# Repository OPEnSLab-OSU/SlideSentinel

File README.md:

# SlideSentinel

## How to Setup
Install the arduino IDE, follow the adafruit [guide](https://learn.adafruit.com/adafruit-feather-m0-basic-proto/overview), and install LOOM with it dependencies with its guide [here](https://github.com/OPEnSLab-OSU/InternetOfAg/tree/master/Arduino_and_Loom_Setup)

Building the rover and base:
Refer to the schematics in the documentation for building the rover and base. All pins are labeled in the schematic located in Documentation/ProjectSpecifications. Custom printed PCB schematics are located in Integration/Hardware/Base and /Rover. Building and creating of the hardware is managed by the OPEnS lab members. A full list of materials and parts used for all phases of the project is located in the supplemental documentation in the bill of materials (BOM). The software for the hub and nodes are located in "Integration/Base" and "Integration/Rover" respectivly. Load one of the directories into arduino IDE and attach whichever device you are building them compile and export to the arduino.

The spreadsheet visualizer and parser is located at "Integration/Spreadsheet". A setup guide is included within along with some sample data.

The node application which facilitates traffic from the Rock7 servers to google spreadsheets is located at "integration/POSTproxy". A setup guide is included within. The application is active at https://postproxy.azurewebsites.net/. 

The mapping application is located at "SlideSentinelWebClient/myapp". An installation guide is included. This application hooks into the spreadsheet and pulls data to display is on a map. An active version of the map is avaliable [here](http://home.stallkamp.us:8999)

## Directory Layout
- Devices contains development, testing, and drivers for specific devices in the system.
- Documentation contains an assortment of documentation including data sheets, blog posts, notes, and the capstone documentation.
- Integration contains mostly all the up to date and in use code for the project. Some directories within are backups of previous demonstrations of the system in different iterations.
- Phase 1 Legacy Code contains some old hub code when the project was just begining.
- SlideSentinelWebClient contains the node app for the mapping application.

# Slide Sentinel Project Specification Guide

## Base

Specification | Status 
--- | --- 
Power Budget | Draws 150-160mA 
Remote Configuration | Hub can recieve remote configuration data to control the satcom upload cycle time, set verbosity scale, and force a satcom uploads.
Deployment Duration | System must last for 1 month
Range | Base unit will be elevated with reference to the node, one mile distance apart, concrete base.

## Rover

Specification | Status
--- | --- 
Power Budget | Draws ~170 mA, 4.53 mA in low power mode 
Solar Power | Solar power charger supplies ~20mA in shaded enviroments and ~175 mA in direct sunlight
Positional Accuracy | Rover must generate sub-centimeter positional calculations at least once a day, with partial tree cover (RTK fix with RTK ratio of 10)
Deployment Duration | System must last 1 month at 15 minute wake cycles
Accelerometer | Sudden orientation shifts must wake Rover unit up from sleep and trigger positional calculations.

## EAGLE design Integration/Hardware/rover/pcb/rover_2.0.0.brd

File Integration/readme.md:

# Slide Sentinel Phase 1 Prototype

This folder contains all of the code for producing a new Rover and Base station pair. This device is intended for collecting data on landslide movement with sub-centimeter positional accuracy. The system logs rover position at set intervals, and uploads the highest quality positional fix via a satcom upload using the ROCKBLOCK+. 

## Getting Started

Inspect the Rover/Rover.png and Base/Base.png schemtic images for a detailed schematic of all components used in the system build. Using the Arduino IDE load the Base device with Base/Base.ino and the Rover device with Rover/Rover.ino. 

## Hardware

### Base
- ROCKBLOCK+ Iridium Satcom Module
- Freewave Z9-T radio
- RTK - GPS Base

### Rover
- MMA8451 accelerometer with interrups
- DS3231 real time clock with interrupts
- Datalogger
- Latching relay for power management
- Freewave Z9-T radio
- RTK - GPS Rover

## Files
1. **Base:** All files for the Base unit of the system
2. **Rover:** All files for the Rover unit for the system
3. **POSTproxy:** Source code for the post proxy web application. Required for successful Google Spreadsheets HTTP requests.
4. **Spreadsheet:** Google spreadsheet script for displaying recorded data.
5. **EditLib:** Rover unit contains direct library edits. This folder contains copies of editted library files, and original copies of library files for the Base unit.

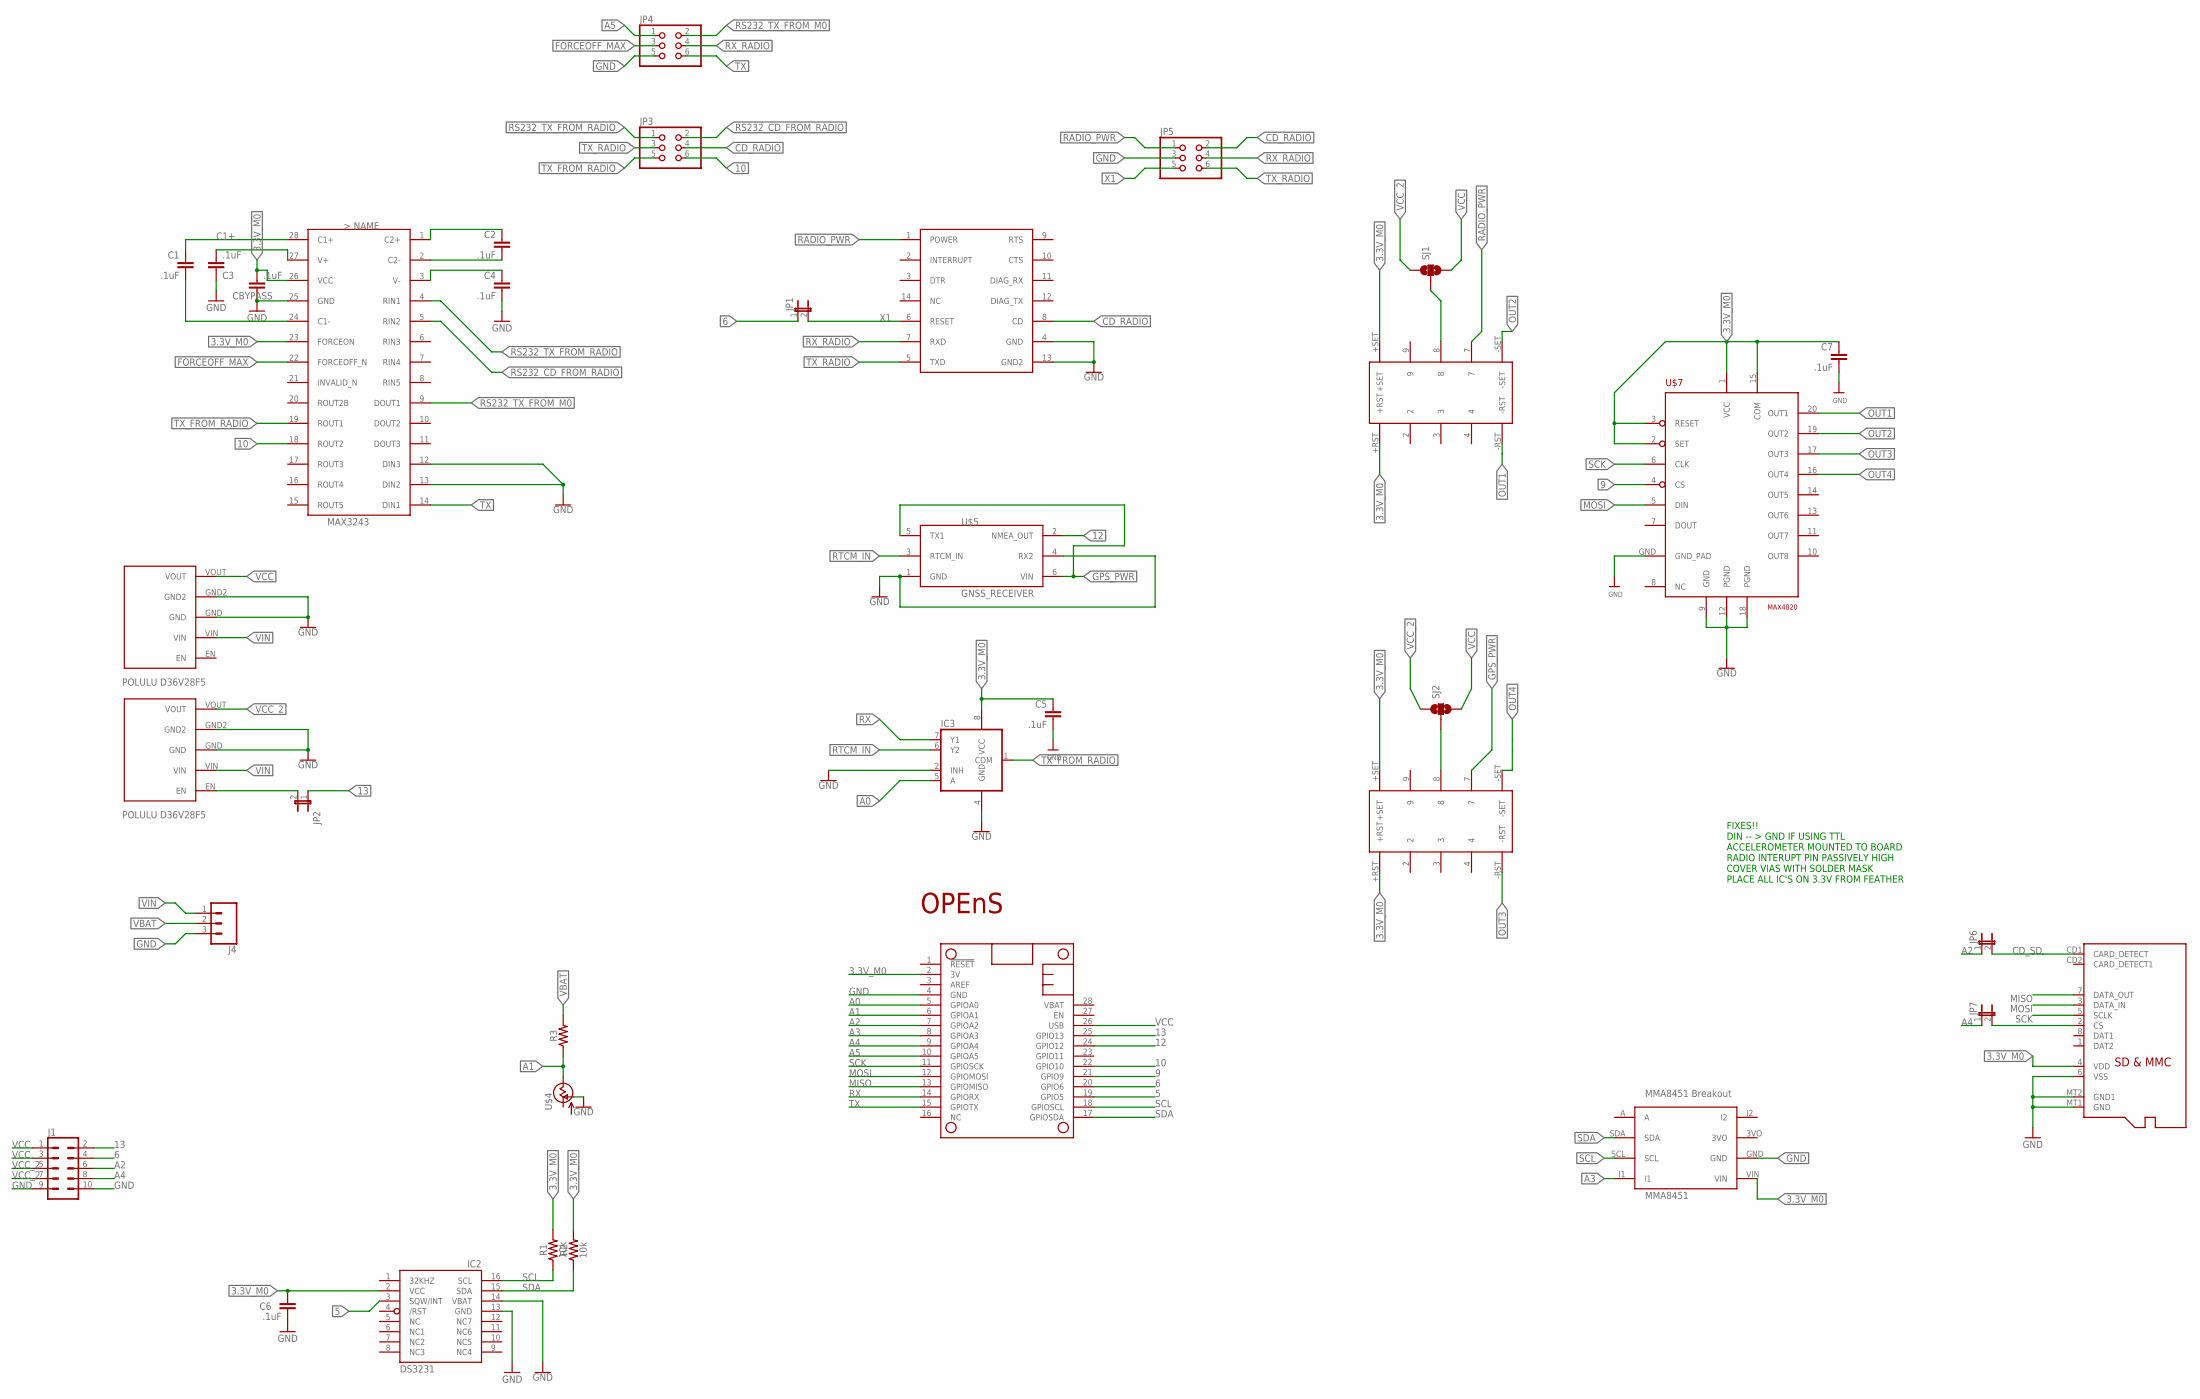
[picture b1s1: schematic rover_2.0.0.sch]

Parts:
C1, C2, C3, C4, C5, C6, C7: .1uF; C1206
CBYPASS: .1uF; C1206
IC2: DS3231/SO; SO16W
IC3: 741G53DCT; DCT_R-PDSO-G8
J1: CONN_05X2NO_SILK; 2X5_NOSILK
J4: CONN_03SCREW; SCREWTERMINAL-3.5MM-3
JP1, JP2, JP6, JP7: JP1E; JP1
JP3, JP4, JP5: PINHD-2X3; 2X03
MS1: FEATHERWING
R1, R2: 10k; 0603
R3: 1.6KOHM-0603-1/10W-1%; 0603
SJ1, SJ2: SOLDERJUMPER_2WAY-OLDT; SJ_2
U$1: MAX3243; SSOP-28
U$2: OPENS-LOGO
U$3, U$12: POLULU_D36V28FX
U$4: CT6EP205; CT6
U$5: GNSS_RECEIVER; HDRV6W64P254_2X3_1016X508X838B
U$7: MAX4820; TSSOP20
U$8, U$9: TQ2SS
U$11: Z9-T/Z9-C
U$13: MMA8451
U$16: MICROSD

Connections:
3.3V_M0: C5.1, C6.1, C7.1, CBYPASS.2, IC2.2 (VCC), IC3.8 (VCC), MS1.2 (3V), R1.2, R2.2, U$1.23 (FORCEON), U$1.26 (VCC), U$7.1 (VCC), U$7.2 (SET), U$7.3 (RESET), U$7.15 (COM), U$8.+RST, U$8.+SET, U$9.+RST, U$9.+SET, U$13.VIN, U$16.4 (VDD)
5: IC2.3 (SQW/INT), MS1.19 (GPIO5)
6: J1.4, JP1.1, MS1.20 (GPIO6)
9: MS1.21 (GPIO9), U$7.4 (CS)
10: JP3.6, MS1.22 (GPIO10), U$1.18 (ROUT2)
12: MS1.24 (GPIO12), U$5.2 (NMEA_OUT)
13: J1.2, JP2.1, MS1.25 (GPIO13)
A0: IC3.5 (A), MS1.5 (GPIOA0)
A1: MS1.6 (GPIOA1), R3.1, U$4.S (VSS)
A2: J1.6, JP6.1, MS1.7 (GPIOA2)
A3: MS1.8 (GPIOA3), U$13.I1
A4: J1.8, JP7.1, MS1.9 (GPIOA4)
A5: JP4.1, MS1.10 (GPIOA5)
C1+: C1.1, U$1.28 (C1+)
CD_RADIO: JP3.4, JP5.2, U$11.8 (CD)
CD_SD: JP6.2, U$16.CD1 (CARD_DETECT)
CS_SD: JP7.2, U$16.2 (CS)
FORCEOFF_MAX: JP4.3, U$1.22 (FORCEOFF_N)
GND: C3.1, C4.2, C5.2, C6.2, C7.2, CBYPASS.1, IC2.13 (GND), IC2.14 (VBAT), IC3.2 (INH), IC3.4 (GND), J1.9, J1.10, J4.3, JP4.5, JP5.3, MS1.4 (GND), U$1.12 (DIN3), U$1.13 (DIN2), U$1.25 (GND), U$3.GND, U$3.GND2, U$4.A (OUT), U$5.1 (GND), U$5.4 (RX2), U$7.9 (GND), U$7.12 (PGND), U$7.18 (PGND), U$7.GND (GND_PAD), U$11.4 (GND), U$11.13 (GND2), U$12.GND, U$12.GND2, U$13.GND, U$16.6 (VSS), U$16.MT1 (GND), U$16.MT2 (GND1)
GPS_PWR: U$5.5 (TX1), U$5.6 (VIN), U$9.7
MISO: MS1.13 (GPIOMISO), U$16.7 (DATA_OUT)
MOSI: MS1.12 (GPIOMOSI), U$7.5 (DIN), U$16.3 (DATA_IN)
unnamed: SJ2.2, U$9.8
unnamed: SJ1.2, U$8.8
unnamed: C2.1, U$1.1 (C2+)
unnamed: C2.2, U$1.2 (C2-)
unnamed: C4.1, U$1.3 (V-)
unnamed: C1.2, U$1.24 (C1-)
unnamed: C3.2, U$1.27 (V+)
OUT1: U$7.20 (OUT1), U$8.-RST
OUT2: U$7.19 (OUT2), U$8.-SET
OUT3: U$7.17 (OUT3), U$9.-RST
OUT4: U$7.16 (OUT4), U$9.-SET
RADIO_PWR: JP5.1, U$8.7, U$11.1 (POWER)
RS232_CD_FROM_RADIO: JP3.2, U$1.5 (RIN2)
RS232_TX_FROM_M0: JP4.2, U$1.9 (DOUT1)
RS232_TX_FROM_RADIO: JP3.1, U$1.4 (RIN1)
RTCM_IN: IC3.6 (Y2), U$5.3 (RTCM_IN)
RX: IC3.7 (Y1), MS1.14 (GPIORX)
RX_RADIO: JP4.4, JP5.4, U$11.7 (RXD)
SCK: MS1.11 (GPIOSCK), U$7.6 (CLK), U$16.5 (SCLK)
SCL: IC2.16 (SCL), MS1.18 (GPIOSCL), R1.1, U$13.SCL
SDA: IC2.15 (SDA), MS1.17 (GPIOSDA), R2.1, U$13.SDA
TX: JP4.6, MS1.15 (GPIOTX), U$1.14 (DIN1)
TX_FROM_RADIO: IC3.1 (COM), JP3.5, U$1.19 (ROUT1)
TX_RADIO: JP3.3, JP5.6, U$11.5 (TXD)
VBAT: J4.2, R3.2
VCC: J1.1, J1.3, MS1.26 (USB), SJ1.3, SJ2.3, U$3.VOUT
VCC_2: J1.5, J1.7, SJ1.1, SJ2.1, U$12.VOUT
VIN: J4.1, U$3.VIN, U$12.VIN
X1: JP1.2, JP5.5, U$11.6 (RESET)
X2: JP2.2, U$12.EN

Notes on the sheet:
FIXES!! DIN -- > GND IF USING TTL ACCELEROMETER MOUNTED TO BOARD RADIO INTERUPT PIN PASSIVELY HIGH COVER VIAS WITH SOLDER MASK PLACE ALL IC'S ON 3.3V FROM FEATHER

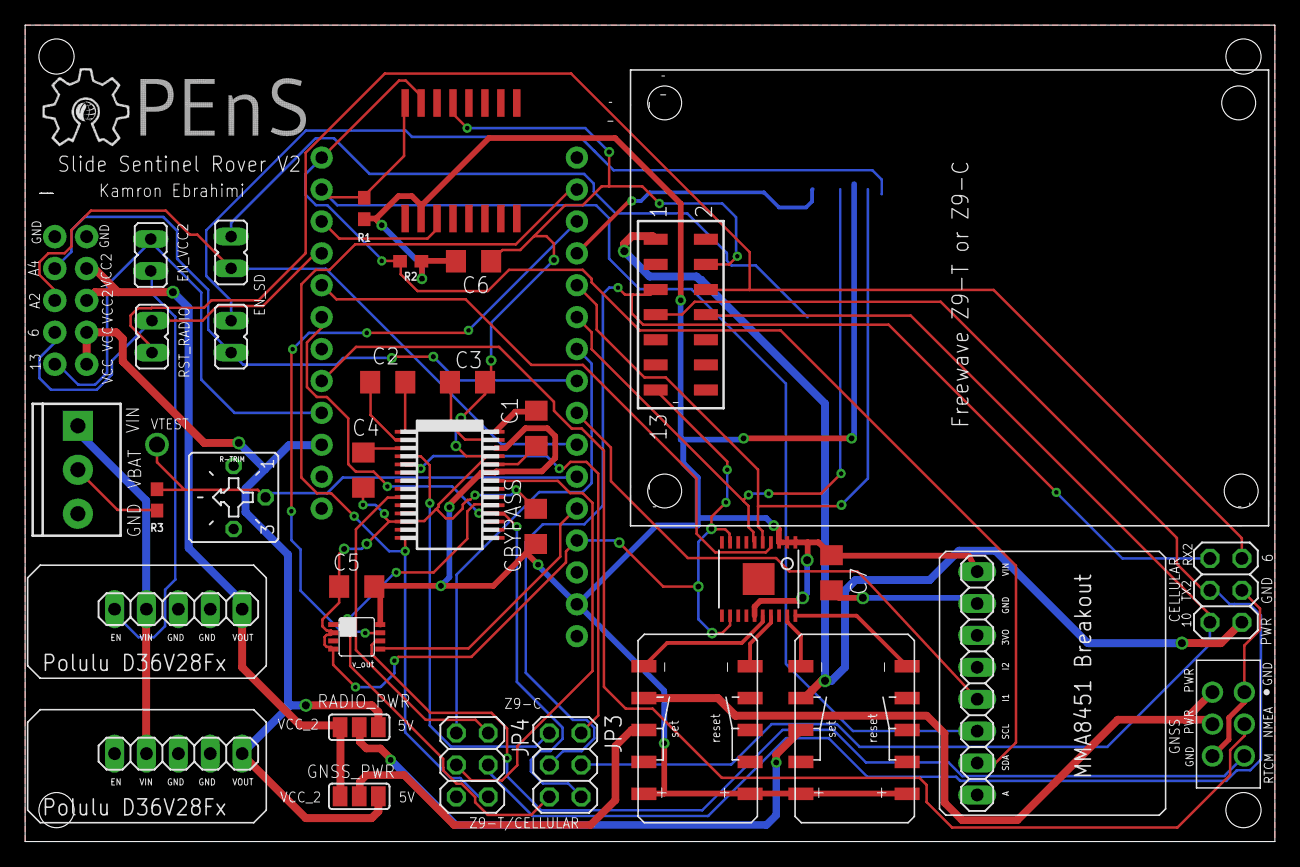
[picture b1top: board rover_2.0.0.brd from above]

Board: 2 copper layers, 99.5 x 65.0 mm, 37 parts (1 on the bottom side), 52 nets.

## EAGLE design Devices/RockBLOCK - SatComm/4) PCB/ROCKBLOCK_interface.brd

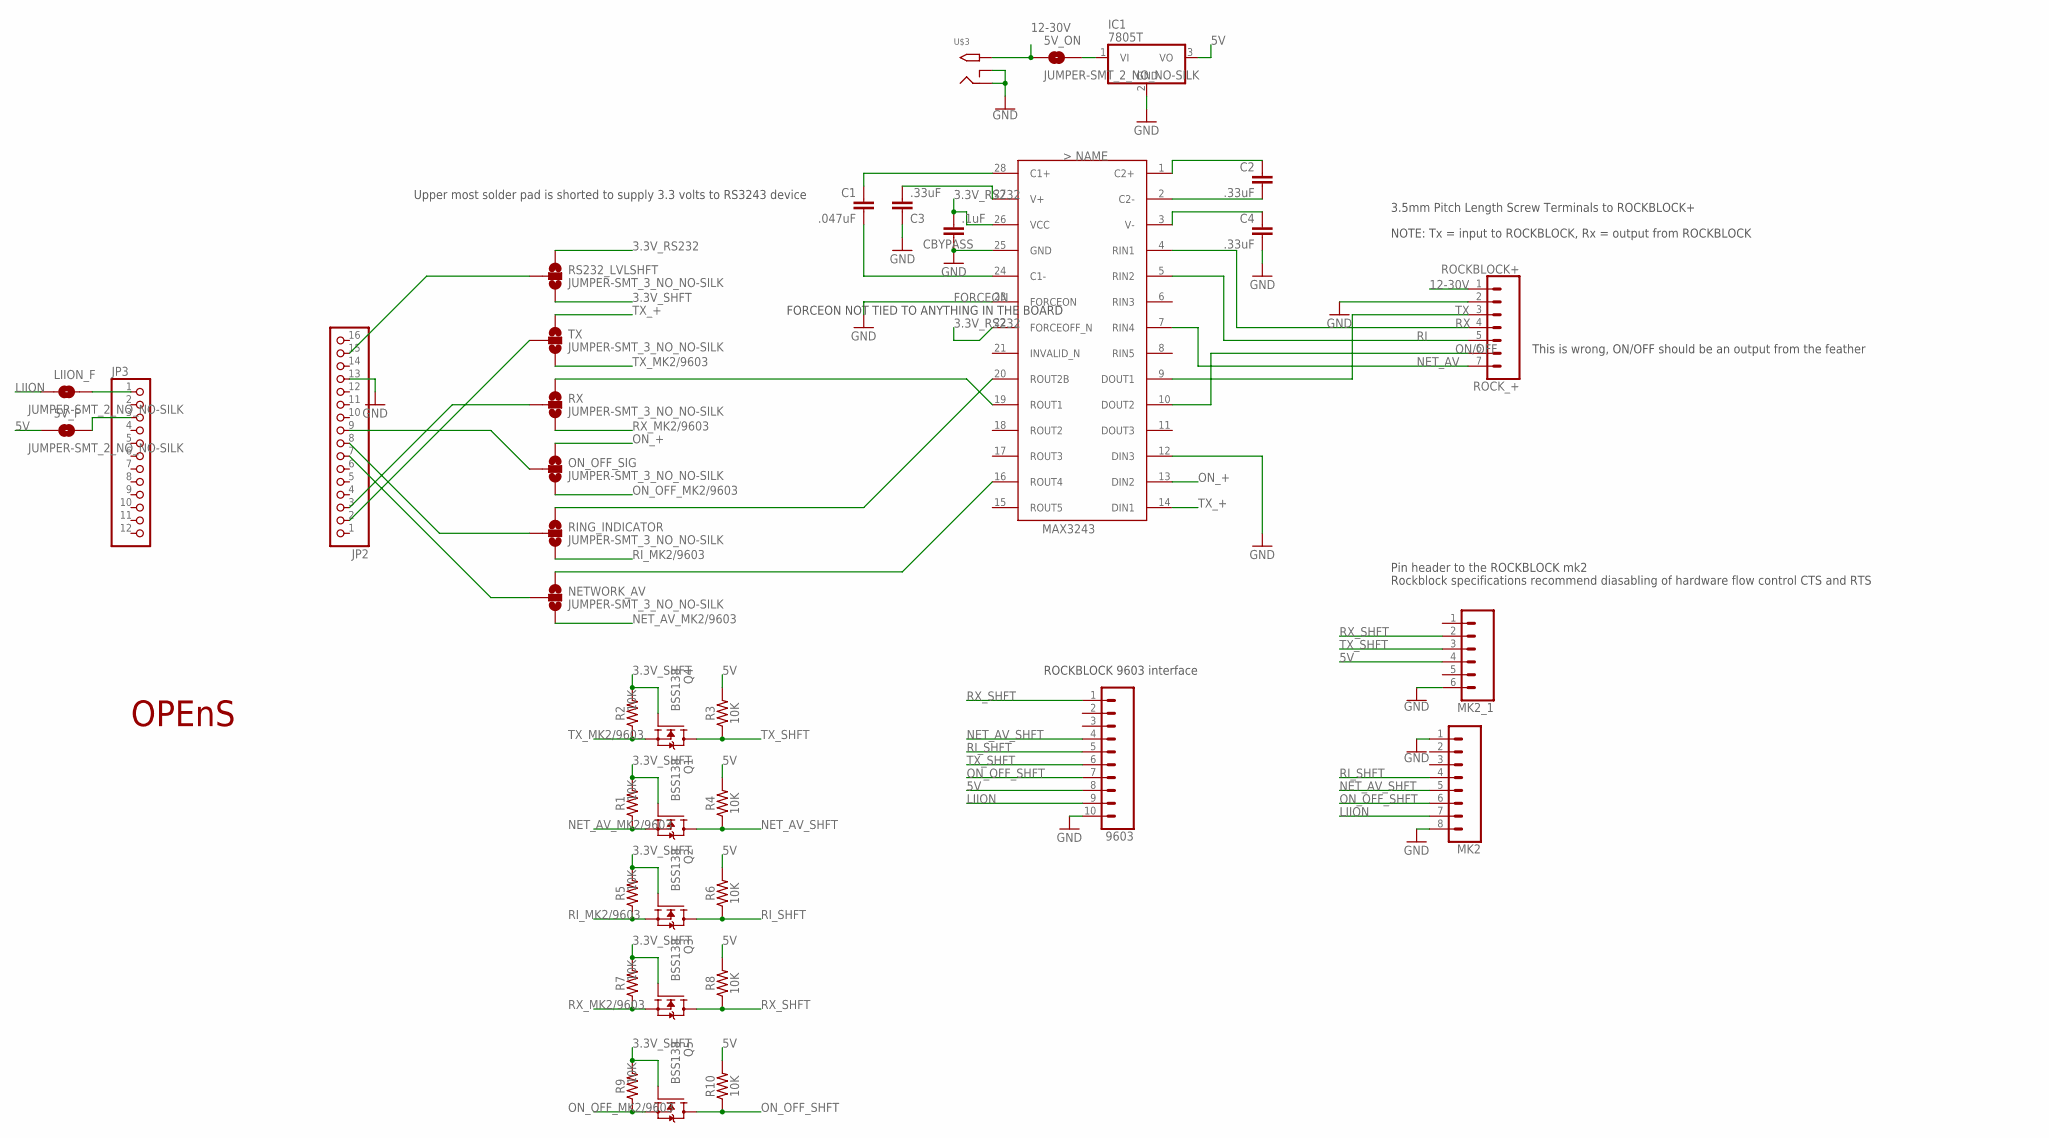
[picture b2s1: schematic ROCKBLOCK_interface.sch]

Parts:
5V_F, 5V_ON: JUMPER-SMT_2_NO_NO-SILK; SMT-JUMPER_2_NO_NO-SILK
9603: CONN_10"; 1X10
C1: .047uF; C1206
C2, C3, C4: .33uF; C1206
CBYPASS: .1uF; C1206
IC1: 7805T; TO220H
JP2: PINHD-1X16; 1X16
JP3: PINHD-1X12; 1X12
LIION_F: JUMPER-SMT_2_NO_NO-SILK; SMT-JUMPER_2_NO_NO-SILK
MK2: CONN_08NO_SILK_FEMALE_PTH; 1X08_NO_SILK
MK2_1: CONN_06NO_SILK_FEMALE_PTH; 1X06_NO_SILK
NETWORK_AV: JUMPER-SMT_3_NO_NO-SILK; SMT-JUMPER_3_NO_NO-SILK
ON_OFF_SIG: JUMPER-SMT_3_NO_NO-SILK; SMT-JUMPER_3_NO_NO-SILK
Q1, Q2, Q3, Q4, Q5: BSS138; SOT23
R1, R2, R3, R4, R5, R6, R7, R8, R9, R10: 10K; 0603
RING_INDICATOR: JUMPER-SMT_3_NO_NO-SILK; SMT-JUMPER_3_NO_NO-SILK
ROCK_+: ROCKBLOCK+; SCREWTERMINAL-3.5MM-7
RS232_LVLSHFT: JUMPER-SMT_3_NO_NO-SILK; SMT-JUMPER_3_NO_NO-SILK
RX: JUMPER-SMT_3_NO_NO-SILK; SMT-JUMPER_3_NO_NO-SILK
TX: JUMPER-SMT_3_NO_NO-SILK; SMT-JUMPER_3_NO_NO-SILK
U$1: MAX3243; SSOP-28
U$2: OPENS-LOGO
U$3: 2.1MMJACKTHM; PJ-102A

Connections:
3.3V_RS232: CBYPASS.2, RS232_LVLSHFT.1, U$1.22 (FORCEOFF_N), U$1.26 (VCC)
3.3V_SHFT: Q1.1 (G), Q2.1 (G), Q3.1 (G), Q4.1 (G), Q5.1 (G), R1.2, R2.2, R5.2, R7.2, R9.2, RS232_LVLSHFT.3
5V: 5V_F.1, 9603.8, IC1.3 (VO), MK2_1.4, R3.2, R4.2, R6.2, R8.2, R10.2
12-30V: 5V_ON.1, ROCK_+.1, U$3.TIP
C1+: C1.1, U$1.28 (C1+)
FORCEON: U$1.23 (FORCEON)
GND: 9603.10, C3.1, C4.2, CBYPASS.1, IC1.2 (GND), JP2.13, MK2.1, MK2.8, MK2_1.6, ROCK_+.2, U$1.12 (DIN3), U$1.25 (GND), U$3.RING, U$3.RING_SW
LIION: 9603.9, LIION_F.1, MK2.7
unnamed: C2.1, U$1.1 (C2+)
unnamed: C2.2, U$1.2 (C2-)
unnamed: C4.1, U$1.3 (V-)
unnamed: JP2.2, TX.2
unnamed: 5V_F.2, JP3.3
unnamed: C1.2, U$1.24 (C1-)
unnamed: RX.1, U$1.19 (ROUT1)
unnamed: JP2.3, RX.2
unnamed: C3.2, U$1.27 (V+)
unnamed: JP2.7, NETWORK_AV.2
unnamed: JP3.1, LIION_F.2
unnamed: NETWORK_AV.1, U$1.16 (ROUT4)
unnamed: JP2.8, RING_INDICATOR.2
unnamed: JP2.9, ON_OFF_SIG.2
unnamed: 5V_ON.2, IC1.1 (VI)
unnamed: JP2.15, RS232_LVLSHFT.2
unnamed: RING_INDICATOR.1, U$1.20 (ROUT2B)
NET_AV: ROCK_+.7, U$1.7 (RIN4)
NET_AV_MK2/9603: NETWORK_AV.3, Q1.2 (S), R1.1
NET_AV_SHFT: 9603.4, MK2.5, Q1.3 (D), R4.1
ON/OFF: ROCK_+.6, U$1.10 (DOUT2)
ON_+: ON_OFF_SIG.1, U$1.13 (DIN2)
ON_OFF_MK2/9603: ON_OFF_SIG.3, Q5.2 (S), R9.1
ON_OFF_SHFT: 9603.7, MK2.6, Q5.3 (D), R10.1
RI: ROCK_+.5, U$1.5 (RIN2)
RI_MK2/9603: Q2.2 (S), R5.1, RING_INDICATOR.3
RI_SHFT: 9603.5, MK2.4, Q2.3 (D), R6.1
RX: ROCK_+.4, U$1.4 (RIN1)
RX_MK2/9603: Q3.2 (S), R7.1, RX.3
RX_SHFT: 9603.1, MK2_1.2, Q3.3 (D), R8.1
TX: ROCK_+.3, U$1.9 (DOUT1)
TX_+: TX.1, U$1.14 (DIN1)
TX_MK2/9603: Q4.2 (S), R2.1, TX.3
TX_SHFT: 9603.6, MK2_1.3, Q4.3 (D), R3.1

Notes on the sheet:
NOTE: Tx = input to ROCKBLOCK, Rx = output from ROCKBLOCK
3.5mm Pitch Length Screw Terminals to ROCKBLOCK+
Pin header to the ROCKBLOCK mk2
Upper most solder pad is shorted to supply 3.3 volts to RS3243 device
Rockblock specifications recommend diasabling of hardware flow control CTS and RTS
ROCKBLOCK 9603 interface
This is wrong, ON/OFF should be an output from the feather
FORCEON NOT TIED TO ANYTHING IN THE BOARD

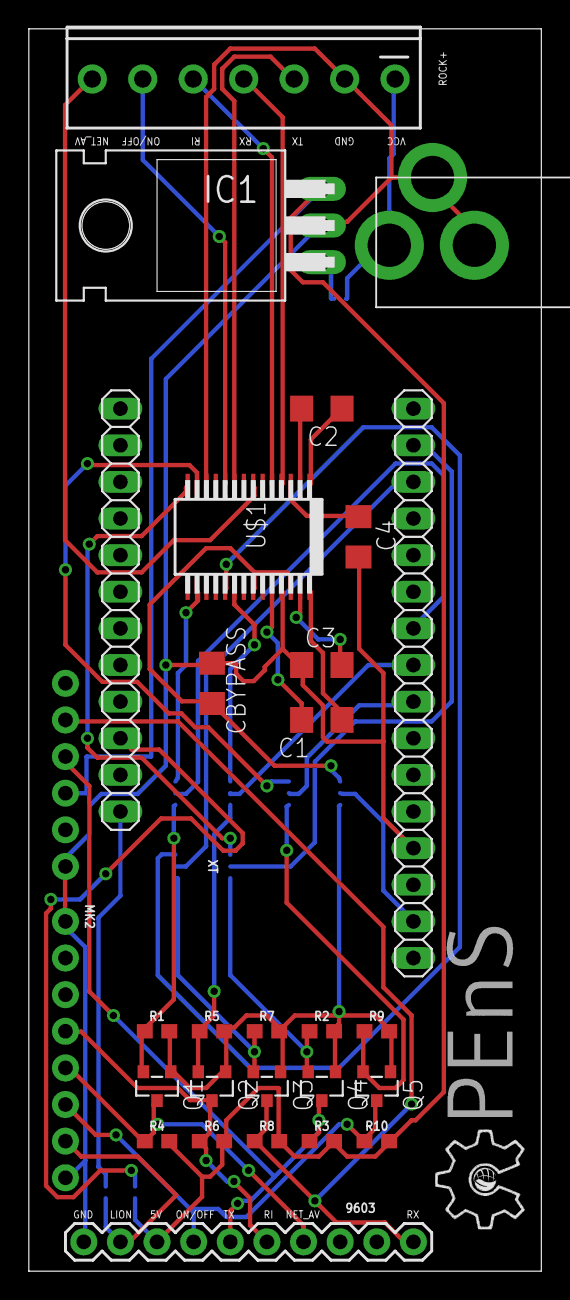
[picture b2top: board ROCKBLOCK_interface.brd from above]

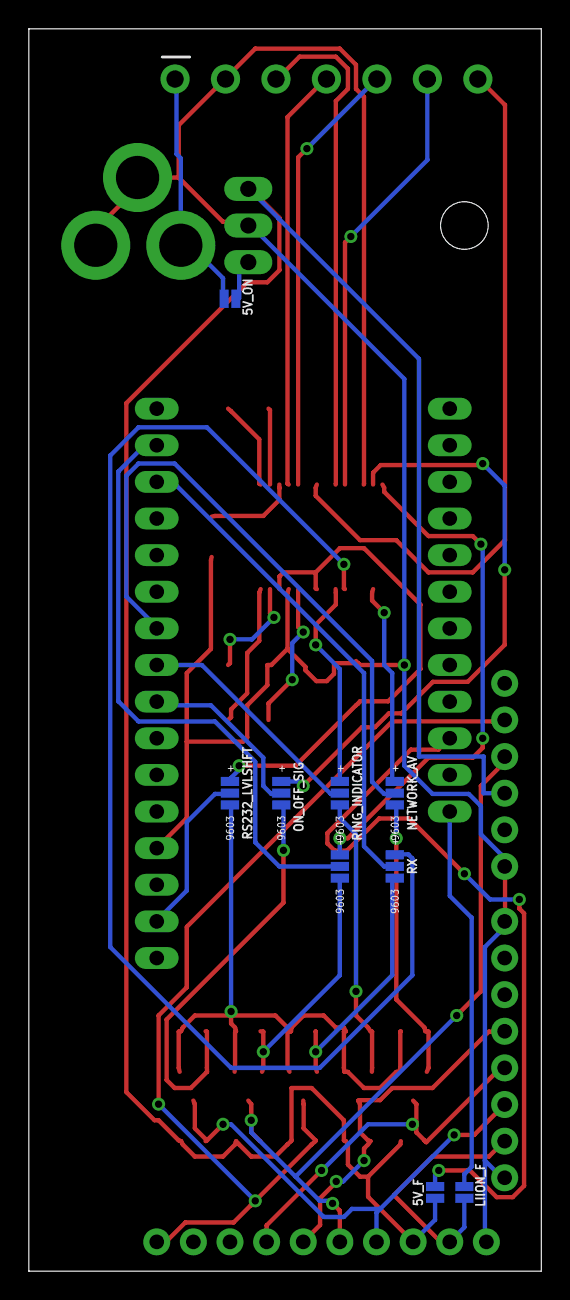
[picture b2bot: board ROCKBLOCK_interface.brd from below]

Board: 2 copper layers, 35.5 x 86.2 mm, 39 parts (9 on the bottom side), 41 nets.

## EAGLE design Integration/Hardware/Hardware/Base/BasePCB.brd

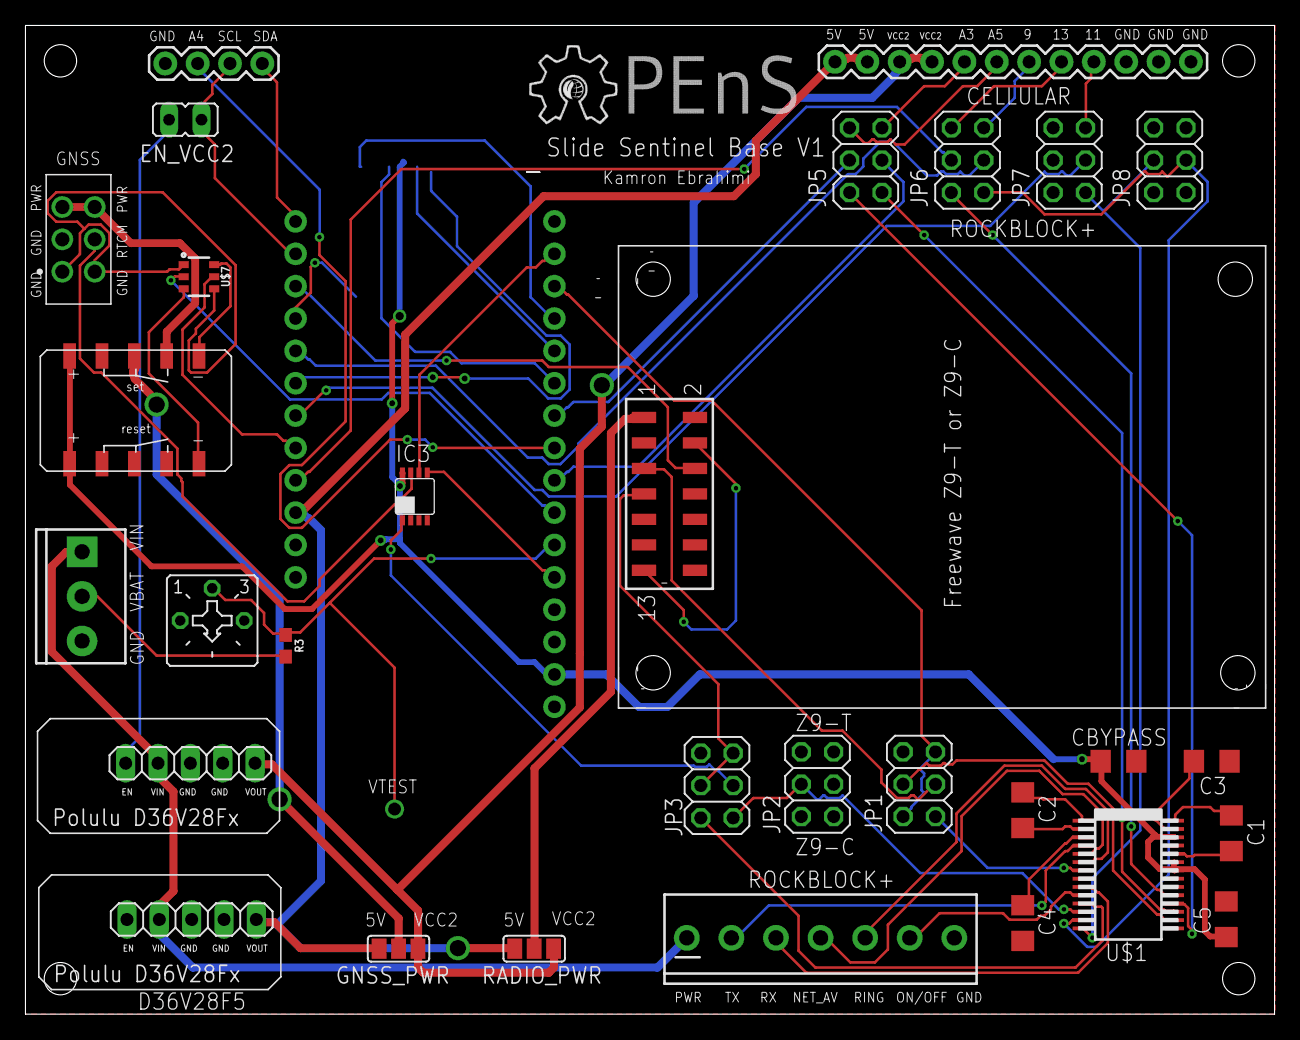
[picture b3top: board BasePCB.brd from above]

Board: 2 copper layers, 98.1 x 77.6 mm, 33 parts (1 on the bottom side), 61 nets.

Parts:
C1, C2, C3, C4, C5: .1uF; C1206
CBYPASS: .1uF; C1206
EN_VCC2: JP1
GNSS_PWR: SJ_2
IC3: 741G53DCT; DCT_R-PDSO-G8
J1: 1X04
J2: 1X12
J4: SCREWTERMINAL-3.5MM-3
JP1, JP2, JP3, JP5, JP6, JP7, JP8: 2X03
MS1: FEATHERWING
R3: 0603
RADIO_PWR: SJ_2
ROCK_+: ROCKBLOCK+; SCREWTERMINAL-3.5MM-7
U$1: MAX3243; SSOP-28
U$2: OPENS-LOGO
U$3, U$12: POLULU_D36V28FX
U$4: MICROSD
U$5: GNSS_RECEIVER; HDRV6W64P254_2X3_1016X508X838B
U$7: DRDC3105; SOT26
U$8: TQ2SS
U$9: CT6EP205; CT6
U$11: Z9-T/Z9-C

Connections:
3.3V_M0: C5.1, CBYPASS.2, IC3.8, MS1.2, U$1.22, U$1.23, U$1.26, U$4.4, U$8.+RST, U$8.+SET
5: MS1.19, U$11.6
6: MS1.20, U$4.CD1
9: JP6.3, MS1.21
9_CELL_ONOFF: J2.6, JP6.5
9_ROCK: JP6.1, JP8.3, U$1.13
10: MS1.22, U$4.2
11: JP7.3, MS1.23
11_CELL_TX: J2.4, JP7.5
11_ROCK: JP7.1, JP8.4, U$1.14
12: MS1.24, U$7.IN1
13: JP6.4, MS1.25
13_CELL_RX: J2.5, JP6.6
13_ROCK: JP6.2, U$1.19
A0: IC3.5, MS1.5
A1: MS1.6, R3.1, U$9.S
A2: MS1.7, U$7.IN2
A3: JP5.3, MS1.8
A3_CELL_RINGAL: J2.8, JP5.5
A3_ROCK: JP5.1, U$1.17
A4: J1.2, MS1.9
A5: JP5.4, MS1.10
A5_CELL_NETAV: J2.7, JP5.6
A5_ROCK: JP5.2, U$1.18
C1+: C1.1, U$1.28
GND: C3.1, C4.2, C5.2, CBYPASS.1, IC3.2, IC3.4, J1.1, J2.1, J2.2, J2.3, J4.3, JP2.6, JP8.5, JP8.6, MS1.4, ROCK_+.7, U$1.25, U$3.GND, U$3.GND2, U$4.6, U$4.MT1, U$4.MT2, U$5.1, U$5.2, U$5.6, U$7.GND1, U$7.GND2, U$9.A, U$11.4, U$11.13, U$12.GND, U$12.GND2
GNSS_PWR: U$5.3, U$5.4, U$8.7
MISO: MS1.13, U$4.7
MOSI: MS1.12, U$4.3
unnamed: GNSS_PWR.2, U$8.8
unnamed: C2.1, U$1.1
unnamed: C2.2, U$1.2
unnamed: U$7.OUT2, U$8.-RST
unnamed: U$7.OUT1, U$8.-SET
unnamed: EN_VCC2.2, U$12.EN
unnamed: C4.1, U$1.3
unnamed: C1.2, U$1.24
unnamed: C3.2, U$1.27
RADIO_PWR: RADIO_PWR.2, U$11.1
RADIO_RX_RS232: JP2.4, JP3.1, U$1.12
RADIO_RX_SIG: IC3.1, JP3.3
RADIO_TX: JP1.3, U$11.5
RADIO_TX_RS232: JP1.1, U$1.7
ROCK_NETAV: ROCK_+.4, U$1.5
ROCK_ONOFF: ROCK_+.6, U$1.10
ROCK_RINGAL: ROCK_+.5, U$1.6
ROCK_RX: ROCK_+.3, U$1.9
ROCK_TX: ROCK_+.2, U$1.4
RS232_TO_RADIO: JP3.2, U$1.11
RTCM_OUT: IC3.7, U$5.5
RX: JP1.2, JP1.5, MS1.14
RX_RADIO: JP3.4, JP3.5, U$11.7
RX_RS232: JP1.4, U$1.16
SCK: MS1.11, U$4.5
SCL: EN_VCC2.1, J1.3, MS1.18
SDA: J1.4, MS1.17
TX: IC3.6, MS1.15
VBAT: J4.2, R3.2
VCC: GNSS_PWR.1, J2.11, J2.12, MS1.26, RADIO_PWR.1, U$3.VOUT
VCC_2: GNSS_PWR.3, J2.9, J2.10, RADIO_PWR.3, U$12.VOUT
VIN: J4.1, ROCK_+.1, U$3.VIN, U$12.VIN

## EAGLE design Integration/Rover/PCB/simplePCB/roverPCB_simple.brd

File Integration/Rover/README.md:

# For PCB design

For PCB design specifically for the RTK device:
  A 50 ohm impedence is required for the RF Signal Path. Vias can cause the impedence to
  slightly decrease, decreasing the quality of the signal. Thus, it is important to try and
  keep a direct line on the same level for the PCB design. The RF Ground and Power can use
  Viasses. Also another note is to to not use 90 degree angles, use two 45 deg angles or a 
  round bend for the signal path.
  
  The pin # is 17 and pin name is RFIN.

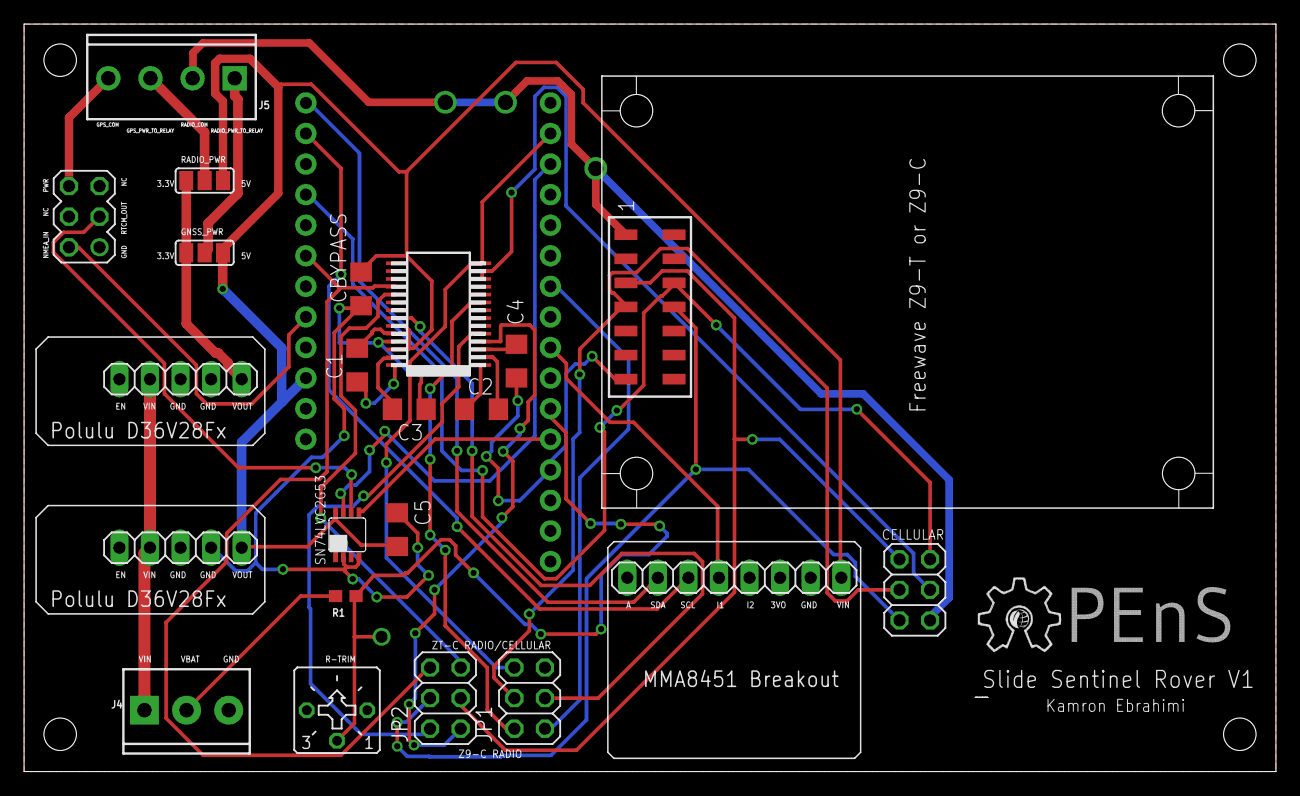
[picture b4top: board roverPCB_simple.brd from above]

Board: 2 copper layers, 104.0 x 62.1 mm, 24 parts (0 on the bottom side), 35 nets.

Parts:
C1, C2, C3, C4, C5: .1uF; C1206
CBYPASS: .1uF; C1206
J4: SCREWTERMINAL-3.5MM-3
J5: SCREWTERMINAL-3.5MM-4
JP1, JP2, JP3: 2X03
MS1: FEATHERWING
R1: 1000000; 0603
SJ1, SJ2: SJ_2
SN74LVC2G53: 741G53DCT; DCT_R-PDSO-G8
U$1: MAX3243; SSOP-28
U$2: OPENS-LOGO
U$3: Z9-T/Z9-C
U$4: CT6EP205; CT6
U$5: GNSS_RECEIVER; MA03-2
U$7, U$8: POLULU_D36V28FX
U$9: MMA8451

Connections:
6: JP3.5, MS1.20, U$3.6
10: JP2.6, MS1.22, U$1.18
12: MS1.24, U$5.2
A0: MS1.5, SN74LVC2G53.5
A1: MS1.6, R1.1, U$4.S
A3: MS1.8, U$9.I1
A5: JP1.1, MS1.10
C1+: C1.1, U$1.28
CD_RADIO: JP2.4, JP3.2, U$3.8
FORCEOFF_MAX: JP1.3, U$1.22
GND: C3.1, C4.2, C5.2, CBYPASS.1, J4.3, JP1.5, JP3.3, MS1.4, SN74LVC2G53.2, SN74LVC2G53.4, U$1.12, U$1.13, U$1.25, U$3.4, U$3.13, U$4.A, U$5.1, U$7.GND, U$7.GND2, U$8.GND, U$8.GND2, U$9.GND
GPS_PWR: J5.4, U$5.6
unnamed: C2.1, U$1.1
unnamed: C2.2, U$1.2
unnamed: J5.1, SJ1.2
unnamed: C4.1, U$1.3
unnamed: C1.2, U$1.24
unnamed: J5.3, SJ2.2
unnamed: C3.2, U$1.27
RADIO_PWR: J5.2, JP3.1, U$3.1
RS232_CD_FROM_RADIO: JP2.2, U$1.5
RS232_TX_FROM_M0: JP1.2, U$1.9
RS232_TX_FROM_RADIO: JP2.1, U$1.4
RTCM_IN: SN74LVC2G53.6, U$5.3
RX: MS1.14, SN74LVC2G53.7
RX_RADIO: JP1.4, JP3.4, U$3.7
SCL: MS1.18, U$9.SCL
SDA: MS1.17, U$9.SDA
TX: JP1.6, MS1.15, U$1.14
TX_FROM_RADIO: JP2.5, SN74LVC2G53.1, U$1.19
TX_RADIO: JP2.3, JP3.6, U$3.5
VBAT: J4.2, R1.2
VCC: C5.1, CBYPASS.2, MS1.26, SJ1.3, SJ2.3, SN74LVC2G53.8, U$1.23, U$1.26, U$7.VOUT, U$9.VIN
VCC_2: SJ1.1, SJ2.1, U$8.VOUT
VIN: J4.1, U$7.VIN, U$8.VIN

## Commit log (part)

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2019-03-21 added node ID to state data, included delay for sending state information
2019-03-22 Node is ready for test deployment
2019-03-25 adjusted hub code for new message format
2019-04-01 corrected battery voltage reading and reset wake times to 5 minutes
2019-04-02 change to battery voltage reading was incorrect
2019-04-07 added send delay for state message to ensure transmission completes before shutdown
2019-04-09 final commit of postproxy, site hosted on azure
2019-04-09 Pushing web client files to repo. The web client can load data from a given spreadsheet and visualize that data over a google maps area. In progress is working on different shades of markers.
2019-04-12 added CRC32 checksum for message verification
2019-04-12 OSC messages do not support uint32, convert to string first
2019-04-14 fixed issues with CRC
2019-04-14 Adding EAGLE schematic for the node
2019-04-15 fixing node modyles again
2019-04-15 added checksum to State messages
2019-04-15 hub status updates provide sd size, node wake time and next satcom upload
2019-04-15 small bug fix
2019-04-16 Update README.md
    guide on settings up the system
2019-04-16 Update README.md
    setup guide
2019-04-16 cleaned up capstone documents and added revised copies of requirements and design
2019-04-18 final versions of documents with sig lines and short spring progress report
2019-04-19 schematics and readme build guide revision
2019-04-22 reorganized github structure, updates readmes, cleaned up unnecessary files, added project specifications in Documentation readme
2019-04-22 fixed readme
2019-04-26 fixed retry routine
2019-05-17 remove WTD
2019-05-24 cleaned up data pipeline, verifying all NMEA checksums
2019-05-28 Added the stat Scripts
2019-07-11 moved UART3 functionality to UART1
2019-10-21 added photos of hardware, base now uses serial1
2019-10-22 added updates photos
2019-10-29 adding newest PCB
2019-11-20 Added SN74LVC2G53 Class, PCB needs to be fixed
2019-11-21 editted photos
2019-11-25 added photo
2019-11-25 added photo for wiki
2019-12-03 restructured files
2020-01-14 Added debug logging utilities and PMC
2020-01-16 com controller complete
2020-01-18 comController working with mock, be careful about jumper contact
2020-01-25 Comcontroller complete
2020-02-04 adding support for Swift Binary Protocol, currently constructing GNSS Controller class
2020-02-11 working on GNSSController, removed Tutorial file all GNSS operations are in SwiftPiksi files, code pushed is stable
2020-02-14 GNSS Controller now updates best current positional value
2020-02-16 successfully wrapped ISR in IMUController class, unfortunatley the interrupt pin cannot be passed and initialized through the constructor
2020-02-18 RTC now using compile time, cleaned up definitions of variables
2020-02-21 alpha functionality complete on FSController, the class constructs new timstamped directories for every wake cycle and initializes the directory with files for GNSS logs, state logs and error message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
2020-02-21 Logging positions collected by GNSS controller using FSController log() method, simplified error message and state handling into logs, added ACCEL wake ID inRTS signal, base needs to verify that the 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
2020-02-22 migrated Blake's RTCController to this branch to prevent merge conflicts, tuned up the RTCController API, added semantic versioning to the pcb files, added semantic versioning to the pin def config f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
2020-02-25 using PIO built in lib manager
2020-03-03 completed model, writing tests, finalizing code design
2020-03-09 reliable data gram interface library capable of both sending and receiving variable length data packets
2020-03-10 completed alpha functionality on rover, still several bugs that need addressing but state machine, uploads, configuration are working
2020-03-16 Add submodules for ArduinoJson and Adafruit_MMA8451
2020-03-16 desubmodule heavily modified library
2020-03-17 remove tinyfsm from submodules
2020-03-17 add tinyFSM back as raw library (sad)
2020-03-17 Bump minimist from 1.2.0 to 1.2.5 in /SlideSentinelWebClient/myapp
    Bumps [minimist](https://github.com/substack/minimist) from 1.2.0 to 1.2.5.
    - [Release notes](https://github.com/substack/minimist/releases)
    - [Commits](https://github.com/substack/minimist/compare/1.2.0...1.2.5)
2020-03-17 Split hardware/software libraries to create unified testing approach, add testing support for desktop
2020-03-28 update travis to run build tests
2020-03-28 switch ldf mode to deep for compatibility
2020-03-30 stage 2 of fixing case sensitivity issues with COM controller
2020-04-03 remove automatic type inference since it is not supported without RTTI, need to figure out a clever way of storing class information on each event
2020-04-04 Added stencils for PCB designs
2020-04-16 Bump https-proxy-agent in /SlideSentinelWebClient/myapp
    Bumps [https-proxy-agent](https://github.com/TooTallNate/node-https-proxy-agent) from 2.2.1 to 2.2.4.
    - [Release notes](https://github.com/TooTallNate/node-https-proxy-agent/releases)
    - [Commits](https://github.com/TooTallNate/node-https-proxy-agent/compare/2.2.1...2.2.4)
2020-04-17 Move object size storage to CircularHeap for less confusion
2020-04-21 Rework testing assertions and structure, write tests for EventQueue
2020-04-22 Minor cleanup
2020-04-24 add UML diagrams of SatComm modules
2020-04-27 added fix
2020-05-08 Move iridiumSBD library to user libraries to allow modification
2020-05-08 Fix iriduim not properly clearing the TX buffer, fix bugs with SatComm tests
2020-05-13 added empty class optimization to eventqueue
2020-05-13 Add file with notes on using the particle debugger
2020-05-26 move relevant files from SlideSentinelRover to SlideSentinelBase
2020-05-26 Attempt 2 at updated travis config
2020-05-26 add SatCommDriver, IriduimSBD, and replace Console with PLOG integration
2020-05-27 switch to compile-time type inference, minor fixes
2020-05-27 up SDcard speed, add sync calls to main
2020-05-28 Add fscontroller indication system
2020-05-29 Add feathertrace to Base, minor bug fixes
2020-05-29 Add GNSS time synchronization functionality to base, need to add rover
2020-06-01 add missing include
2020-06-02 Add lots of documentation for SatComm
2020-06-03 Add travis badge to readme
2020-06-08 add travis github releases
2020-06-12 remove platformio remote tests from travis temporarily
2020-08-20 Bump bcrypt from 3.0.8 to 5.0.0 in /Integration/POSTproxy
    Bumps [bcrypt](https://github.com/kelektiv/node.bcrypt.js) from 3.0.8 to 5.0.0.
    - [Release notes](https://github.com/kelektiv/node.bcrypt.js/releases)
    - [Changelog](https://github.com/kelektiv/node.bcrypt.js/blob/master/CHANGELOG.md)
    - [Commits](https://github.com/kelektiv/node.bcrypt.js/compare/v3.0.8...v5.0.0)
2020-10-23 code from Cyrus
2020-12-12 Bump ini from 1.3.5 to 1.3.8 in /SlideSentinelWebClient/myapp
    Bumps [ini](https://github.com/isaacs/ini) from 1.3.5 to 1.3.8.
    - [Release notes](https://github.com/isaacs/ini/releases)
    - [Commits](https://github.com/isaacs/ini/compare/v1.3.5...v1.3.8)
2021-02-22 Saving state of Rover documentation... In progress
2021-03-05 Further progress on Rover documentation.
2021-06-21 Organized schematic
2021-08-11 Bump path-parse from 1.0.6 to 1.0.7 in /SlideSentinelWebClient/myapp
    Bumps [path-parse](https://github.com/jbgutierrez/path-parse) from 1.0.6 to 1.0.7.
    - [Release notes](https://github.com/jbgutierrez/path-parse/releases)
    - [Commits](https://github.com/jbgutierrez/path-parse/commits/v1.0.7)
    ---
    updated-dependencies:
    - dependency-name: path-parse
2021-10-20 Add Polulu refactor and comment
2021-11-05 More code changes regarding relays/prepwork for request() function
2021-11-10 Add enum code and Mux function declarations
2021-11-10 Removed some lines from main.cpp in the base code. Removed some extra lines from main.cpp in the rover code.
2021-11-10 Modify FreewaveRadio and add some comments for configuring radios
2021-11-10 Code changes
2021-11-10 Added the new base files.
2021-11-13 Comment additions
2021-11-13 Adding radio support, need to think abt moving config back to src since that makes sense
2022-01-10 Periodic push
2022-01-10 Added Z9C getter function to Freewave
2022-01-12 Copied Base code to allow for a new slate to rewrite
2022-01-14 Cleared the JSON object before storing new data
2022-01-21 Worked on adding a clean SDManger. This wil be used to replace FSController
2022-01-25 Switched diagnostic data to use the Diagnostic class
2022-01-25 Removed unused files, should be able to run-ish now
2022-02-08 Get rover to compile
2022-02-16 Added test code for radio communication.
2022-02-16 Modified the behavior of the radio test code.
    Fix issues with packets not sending and the feather port being unavailable.
2022-02-23 Add roverradiotest code
2022-02-26 Rover::request() correctly serializes and transmits packets.
2022-03-25 Bump minimist from 1.2.0 to 1.2.6 in /SlideSentinelWebClient/myapp
    Bumps [minimist](https://github.com/substack/minimist) from 1.2.0 to 1.2.6.
    - [Release notes](https://github.com/substack/minimist/releases)
    - [Commits](https://github.com/substack/minimist/compare/1.2.0...1.2.6)
    ---
    updated-dependencies:
    - dependency-name: minimist
2022-03-29 Add more GNSSMediator functionallity, taking break before implementing fifo read stuff
2022-06-23 Add supposed gnss readability with gnsscontrollre
2022-06-23 test
2022-06-23 added decimals points to lat and lon
2022-06-24 Add rtc branch and time
2022-06-24 Pause writing sleep code
2022-06-24 Attemp to get feather to wake up from sleep
2022-07-05 Flesh out main a bit more -aleks, write official alarm functions -ben
2022-07-05 Second fix
2022-07-11 New branch
2022-07-18 Clean up program
2022-07-19 Rewrote GNSS Controller
2022-07-20 Casted location data to strings
2022-07-20 Single call to record data
2022-07-21 Update comment
2022-08-05 some changes, but just testing
2022-08-05 polished fscontroller, gnsscontroller and main
2022-08-14 SP fix with max, reduce .h files in main
2022-08-14 Add max files?
2022-08-16 Add functional radiohead code, will need to polish later, specifically base.cpp
2022-08-16 Max sp fix
2022-08-25 Add translator chip, refactor some minor details with radio
2022-08-25 Add simplistic base rtk capability
2022-09-01 One line fixed this branch, superceding the radiotest backup, this is the new main branch
2022-09-07 Flush out rover cycle, require that message handling functions are flushed out, base needs both treatments as well
2022-09-09 Add Will's radio manager code
2022-09-18 Get code to a base level
2022-09-18 Send packet for Base, Receive for Rover
2022-09-18 Rover radio fix
2022-09-18 Initial Base Test #1
2022-09-19 Base sends dummy message to Rover
2022-09-19 2 Way Working Radio for Base
2022-09-19 Fix gnss with Will
2022-09-19 Add will's upload format
2022-09-20 Working radio code with serial
2022-09-21 Stable Base With SD Manager
2022-09-21 Moved RadioHead to local lib
2022-09-22 SatComm work
2022-12-09 Bump express from 4.16.4 to 4.17.3 in /SlideSentinelWebClient/myapp
    Bumps [express](https://github.com/expressjs/express) from 4.16.4 to 4.17.3.
    - [Release notes](https://github.com/expressjs/express/releases)
    - [Changelog](https://github.com/expressjs/express/blob/master/History.md)
    - [Commits](https://github.com/expressjs/express/compare/4.16.4...4.17.3)
    ---
    updated-dependencies:
2023-01-23 SatComm finished (needs testing)
2023-01-31 Quality of life changes to SatComm control
2023-01-31 Fine tuned and removed old SatComm
2023-01-31 Test commit
2023-02-07 add resetGNSSStructs back, rover will now initialize with the proper address, satcomm minify now uses substring instead of loops
2023-02-07 Added simulation and satcomm enable flags to disable code functionality
2023-02-14 Bump node-fetch from 2.6.0 to 2.6.9 in /SlideSentinelWebClient/myapp
    Bumps [node-fetch](https://github.com/node-fetch/node-fetch) from 2.6.0 to 2.6.9.
    - [Release notes](https://github.com/node-fetch/node-fetch/releases)
    - [Commits](https://github.com/node-fetch/node-fetch/compare/v2.6.0...v2.6.9)
    ---
    updated-dependencies:
    - dependency-name: node-fetch
2023-02-15 Rover and Base appear to be functioning
2023-02-16 Only grab the first 6 digits of the seconds when sending over SatComm
2023-02-16 Added additional metadata to GPX files
2023-02-17 Minifying the JSON should work for satcomm
2023-02-18 turn off radio while waiting to transmit data to the base
2023-03-07 Changed rover to continue populating new fixes
2023-03-11 Implemented SatComm RTC time sync

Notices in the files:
parts and their libraries:
SparkFun-Connectors: Licensing: Creative Commons ShareAlike 4.0 International - https://creativecommons.org/licenses/by-sa/4.0
microbuilder: This work is placed in the public domain, and may be freely used for commercial and non-commercial work with the following conditions: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
